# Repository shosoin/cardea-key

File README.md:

# Cardea Key

> *Cardea*, Roman goddess of hinges and thresholds: "her power is to open what is shut and to shut
> what is open" (Ovid, *Fasti* VI).

**Cardea Key** is an open-source security key firmware for the **Raspberry Pi Pico 2** (RP2350). It
combines in a single firmware what usually needs several keys:

- **FIDO2 / WebAuthn passkeys** and **U2F** — passwordless login, second factor, SSH `-sk` keys,
  `pam_u2f`, LUKS (`systemd-cryptenroll`).
- **OpenPGP card** — GnuPG signing, encryption and SSH authentication keys on the key.
- **PIV** — X.509 smart card (VPN client certificates, PKCS#11, Windows smart-card login).
- **OATH** (TOTP/HOTP) — authenticator codes, readable with `ykman oath` / Yubico Authenticator.
- **OTP slots** — static password, HOTP and HMAC-SHA1 challenge-response (e.g. KeePassXC), with
  touch support.
- **Vault** — encrypted, restorable backups of your passkeys, signed off by a CA you control.

Website: <https://cardeakey.org>

> **Status: experimental prototype, not audited.** Phase 0 (one unified firmware, tested on a bare
> Pico 2) and phase 1 (NXP SE051 secure element support) are released as **v0.3.0**. Phase 1 has
> been validated against a simulated SE05x only, **not yet on a real SE051C2** chip. Do not rely on
> it as your only key. Next: tests on the real chip, then a fingerprint sensor. See
> [Roadmap](#roadmap).

## How it is built

Cardea Key is built on the excellent work of **Pol Henarejos**:
[pico-fido](https://github.com/polhenarejos/pico-fido),
[pico-openpgp](https://github.com/polhenarejos/pico-openpgp) and
[pico-keys-sdk](https://github.com/polhenarejos/pico-keys-sdk). It is not affiliated with or
endorsed by the Pico Keys project.

This repository does not fork them. It pins each upstream repository to an exact commit
(`scripts/fetch-sources.sh`) and applies a reviewed set of patches (`patches/`, described in
[patches/README.md](patches/README.md)) to merge both applications into one firmware and to fix
the issues we found while testing, among them:

- **The firmware never writes the RP2350 OTP** unless you explicitly build with
  `HARDEN_HARDWARE=ON`. Upstream writes and locks OTP keys on first boot, which is irreversible.
  With the default build your Pico 2 stays a generic, reusable board.
- **OTP challenge-response with touch over the HID keyboard**, in asynchronous mode as YubiKeys
  do (used for example by KeePassXC). Upstream denies it.
- Bugs we reported were fixed upstream by Pol within a day (user presence really required for
  sign-in, FIDO reset, U2F and OATH "touch" accounts; master-key restore requires the PIN; the
  3-wrong-PINs-per-power-up lock; OTP over HID no longer corrupting the card thread). We follow his
  `main` and dropped our own versions of those fixes; see
  [patches/README.md](patches/README.md#fixes-now-in-upstream-dropped-on-2026-11-02).
- **Vault** with a replaceable root CA (see [docs/vault.md](docs/vault.md)).

## Hardware

- Raspberry Pi **Pico 2** (RP2350). The BOOTSEL button is the user-presence button and the
  on-board LED shows the state: short blinks when idle, **steady on when the key is waiting for a
  touch**.
- Optional: an **NXP SE051C2** secure element on I2C0 (SDA GP4, SCL GP5, address 0x48), e.g. on a
  MIKROE-5392 "SE051 Plug & Trust Click" board, for the `se05x` firmware below.

## Building

Tested on Debian 13 with `arm-none-eabi-gcc` 14.2, CMake 3.31 and Ninja.

```sh
sudo apt install git cmake ninja-build gcc-arm-none-eabi libnewlib-arm-none-eabi \
                 build-essential python3 python3-cryptography
scripts/fetch-sources.sh            # clones upstream at the pinned commits and applies patches/
cmake -G Ninja -S firmware -B build/cardea-key -DPICO_BOARD=pico2 \
      -DPICO_SDK_PATH=$PWD/third_party/pico-sdk
cmake --build build/cardea-key      # -> build/cardea-key/cardea_key.uf2
```

Main build options (`-D<option>=ON|OFF`):

| Option | Default | Meaning |
|---|---|---|
| `HARDEN_HARDWARE` | **OFF** | ON = upstream behaviour: writes and locks OTP keys on first boot. **Irreversible.** |
| `ENABLE_VAULT` | ON | Passkey backups (inactive until each key is enrolled). OFF removes the code. |
| `KEYV2_VAULT_CA_CERT` | Cardea Key Vault CA | Root certificate (PEM) of the vault CA. Point it at your own CA. |
| `FORCE_BUTTON_WAIT` | ON | Require a real button press for user presence. |
| `CARDEA_SE` | `soft` | Secure-element backend. `soft`: no chip, same security and data as v0.1.0. `se05x`: NXP SE051 on I2C (see [Two firmwares](#two-firmwares-soft-and-se05x)). |
| `CARDEA_SE_FALLBACK` | **OFF** | `se05x` only. OFF: without the chip the key does not run (SE FAULT). ON (bench only): it runs on the flash keys instead. |
| `ENABLE_OATH_APP`, `ENABLE_OTP_APP` | ON | OATH and OTP-slot applications. |
| `USB_VID`, `USB_PID` | `0x1209`, `0x0001` | USB IDs (see below). |

## Two firmwares: `soft` and `se05x`

Each release has two builds. **Both are experimental.**

| | `cardea_key-vX.Y.Z-soft.uf2` | `cardea_key-vX.Y.Z-se05x.uf2` |
|---|---|---|
| Hardware | a bare Pico 2 | Pico 2 **plus an SE051C2** wired to GP4/GP5 |
| Root key | master key in the Pico's flash | inside the SE051 (key derivation runs in the chip) |
| PINs and retry counters | in the Pico's flash | inside the SE051 (authentication objects with their own counter; the PIN never crosses the bus) |
| Link to the chip | — | encrypted and authenticated (Platform SCP03) |
| Without the chip | n/a | **SE FAULT**: the key refuses to work (see below) |
| Tested | on the board, all applications | against a simulated SE05x only, not yet on a real chip |

**What the `se05x` build does not do yet.** It runs in *test mode*: the SCP03 channel uses the
SE051C2 factory keys (public), and the master key is also kept in the flash, so that losing the
chip during development does not lose the data. **Today it protects no more than `soft`.** Leaving
test mode (per-device channel keys, root key generated in the chip and removed from the flash)
comes after the real-chip tests.

**SE FAULT.** If the `se05x` build finds no SE051 at power-up (or the root key is not in it), no
application answers, the USB product name ends in "SE FAULT" (it shows up as such in the
smart-card reader name), and the LED flashes three times quickly, then pauses. Nothing is erased:
plug the chip back in and power-cycle. A key in SE FAULT can still be rebooted into BOOTSEL with
`scripts/cardea-bootsel.sh`.

Switching between the two builds on the same Pico keeps the data, but once a PIN has moved into
the chip, the `soft` build can no longer check it.

## Flashing

Download the build you want from the [latest release](https://github.com/shosoin/cardea-key/releases/latest)
(check its SHA-256 in `SHA256SUMS`) or build it yourself. Hold BOOTSEL while plugging the Pico 2
in, then copy the `.uf2` file to the `RP2350` drive. Data
on the key (PIN, credentials) survives firmware updates. A key already running Cardea Key can be
rebooted into BOOTSEL with `scripts/cardea-bootsel.sh` (needs a button press).

## USB IDs and host software

The prototype uses the **pid.codes test ID `1209:0001`**. FIDO2 works out of the box (browsers,
`libfido2`, `python-fido2`). The smart-card applications (OpenPGP, PIV, OATH) go through CCID:
`pcscd`'s CCID driver only loads for known IDs, so add the test ID to its list
(`scripts/libccid-reader.py`, needs root) or use GnuPG's internal CCID driver.

This project **never ships with Yubico's vendor ID**. Some Yubico tools (`ykman otp`) only talk to
keys with that ID; changing the ID in your own build is your choice and your responsibility.

## Vault (passkey backups)

Passkeys normally die with the key. The vault lets you export them, encrypted with a vault key you
keep, and import them into another key enrolled in the same vault. Enrolling a key requires its
PIN, a 10-second button press right after plugging it in, and a certificate for that key's serial
number signed by the vault CA, which is compiled into the firmware. You can build with your own
CA. Details and the `scripts/cardea-vault.py` tool: [docs/vault.md](docs/vault.md).

## Documentation

- [docs/applications.md](docs/applications.md) — what each application is for and how to use it.
- [docs/vault.md](docs/vault.md) — vault design, own CA, enrollment, export and import.
- [patches/README.md](patches/README.md) — every change made to upstream, and why.
- [SECURITY.md](SECURITY.md) — threat model of the prototype and how to report a vulnerability.

## Roadmap

| Phase | What | Status |
|---|---|---|
| 0 | Unify pico-fido and pico-openpgp in one firmware; test on a bare Pico 2 without touching OTP | **done** |
| 1 | NXP SE051C2 secure element: PIN and retry counter in the SE, root key out of the flash | **done** on a simulated chip (v0.2.0; v0.3.0 follows upstream `main`); real-chip tests pending |
| 2 | Fingerprint sensor as user presence, time-limited biometric unlock | planned |
| 3 | Full prototype: Pico 2 + real SE051C2 + fingerprint sensor, tested together as one key | parts on the way |
| 4 | Own PCB (RP2354A + SE051C2 + sensor connector) | **design in progress**: [rev A draft](hardware/README.md), schematic done, placement draft, not routed; manufactured only after phase 3 |

## License

[AGPL-3.0](LICENSE), the license of the upstream projects. Patches and tools in this repository
are released under the same license. The hardware design files in [hardware/](hardware/README.md)
are licensed under [CERN-OHL-S-2.0](hardware/LICENSE). "Pico Keys" is a trademark of its owner; this project does
not use that name.

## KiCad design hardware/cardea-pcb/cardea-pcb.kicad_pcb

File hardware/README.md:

# Cardea Key — hardware (rev A, draft)

> **Work in progress. Not manufactured, not validated.** This is the first draft of Cardea Key's
> own board: the schematic passes KiCad's ERC, and the parts are placed but **not routed yet**.
> It will not be manufactured until the full prototype (Pico 2 + real SE051C2 + fingerprint
> sensor) has been validated. Do not order it.

| | |
|---|---|
| MCU | Raspberry Pi **RP2354A** (RP2350 with 2 MB flash inside) |
| Secure element | NXP **SE051C2** on I2C0 (GP4 SDA, GP5 SCL), with enable (GP6) and reset (GP7) from the MCU |
| Fingerprint sensor | off-board **R502-F Pro**, wires soldered into six 2.54 mm through holes (optional SH1.0 connector in parallel) |
| USB | USB-C receptacle (16 pins) on the board edge, VBUS TVS |
| Power | Diodes AP2112K-3.3 LDO |
| Board | 4 layers, 1.6 mm, about 45 × 20 mm, no screw holes (held by a 3D-printed case) |
| User interface | one push button (C&K KMR2) and an RGB LED; BOOTSEL; SWD on three 2.54 mm holes |

The RP2354A core (core regulator, crystal, decoupling, USB and BOOTSEL) follows Raspberry Pi's
**"RP2350A Minimal"** reference design (© Raspberry Pi Ltd, MIT licence) and the "Hardware design
with RP2350" guide.

## Files

- [`cardea-pcb-schematic-revA.pdf`](cardea-pcb-schematic-revA.pdf): the schematic.
- `cardea-pcb/`: the KiCad 10 project. `cardea-pcb.kicad_sch` is **generated** by
  `tools/gen_schematic.py` from a parts-and-nets table, so the netlist is exactly that table.
  `cardea-pcb.kicad_pcb` is the placement draft from `tools/gen_board.py`. `lib/cardea.kicad_sym`
  holds the SE051C2 symbol, drawn from its datasheet pin table.
- `tools/kicad_lib.py`: reads KiCad library symbols and their pins without KiCad's Python API.
- `images/`: renders of the current draft ([top](images/cardea-pcb-top.png),
  [bottom](images/cardea-pcb-bottom.png)).

```sh
python3 hardware/tools/gen_schematic.py
kicad-cli sch erc --severity-all hardware/cardea-pcb/cardea-pcb.kicad_sch      # must report 0
```

## Licence

The hardware design files in this directory are licensed under the
**CERN Open Hardware Licence Version 2 – Strongly Reciprocal** ([CERN-OHL-S-2.0](LICENSE)).
The firmware and the tools elsewhere in this repository stay under AGPL-3.0.

Symbols and footprints come from the official KiCad libraries (CC-BY-SA 4.0 with their exception
for designs), except the SE051C2 symbol, which is our own.

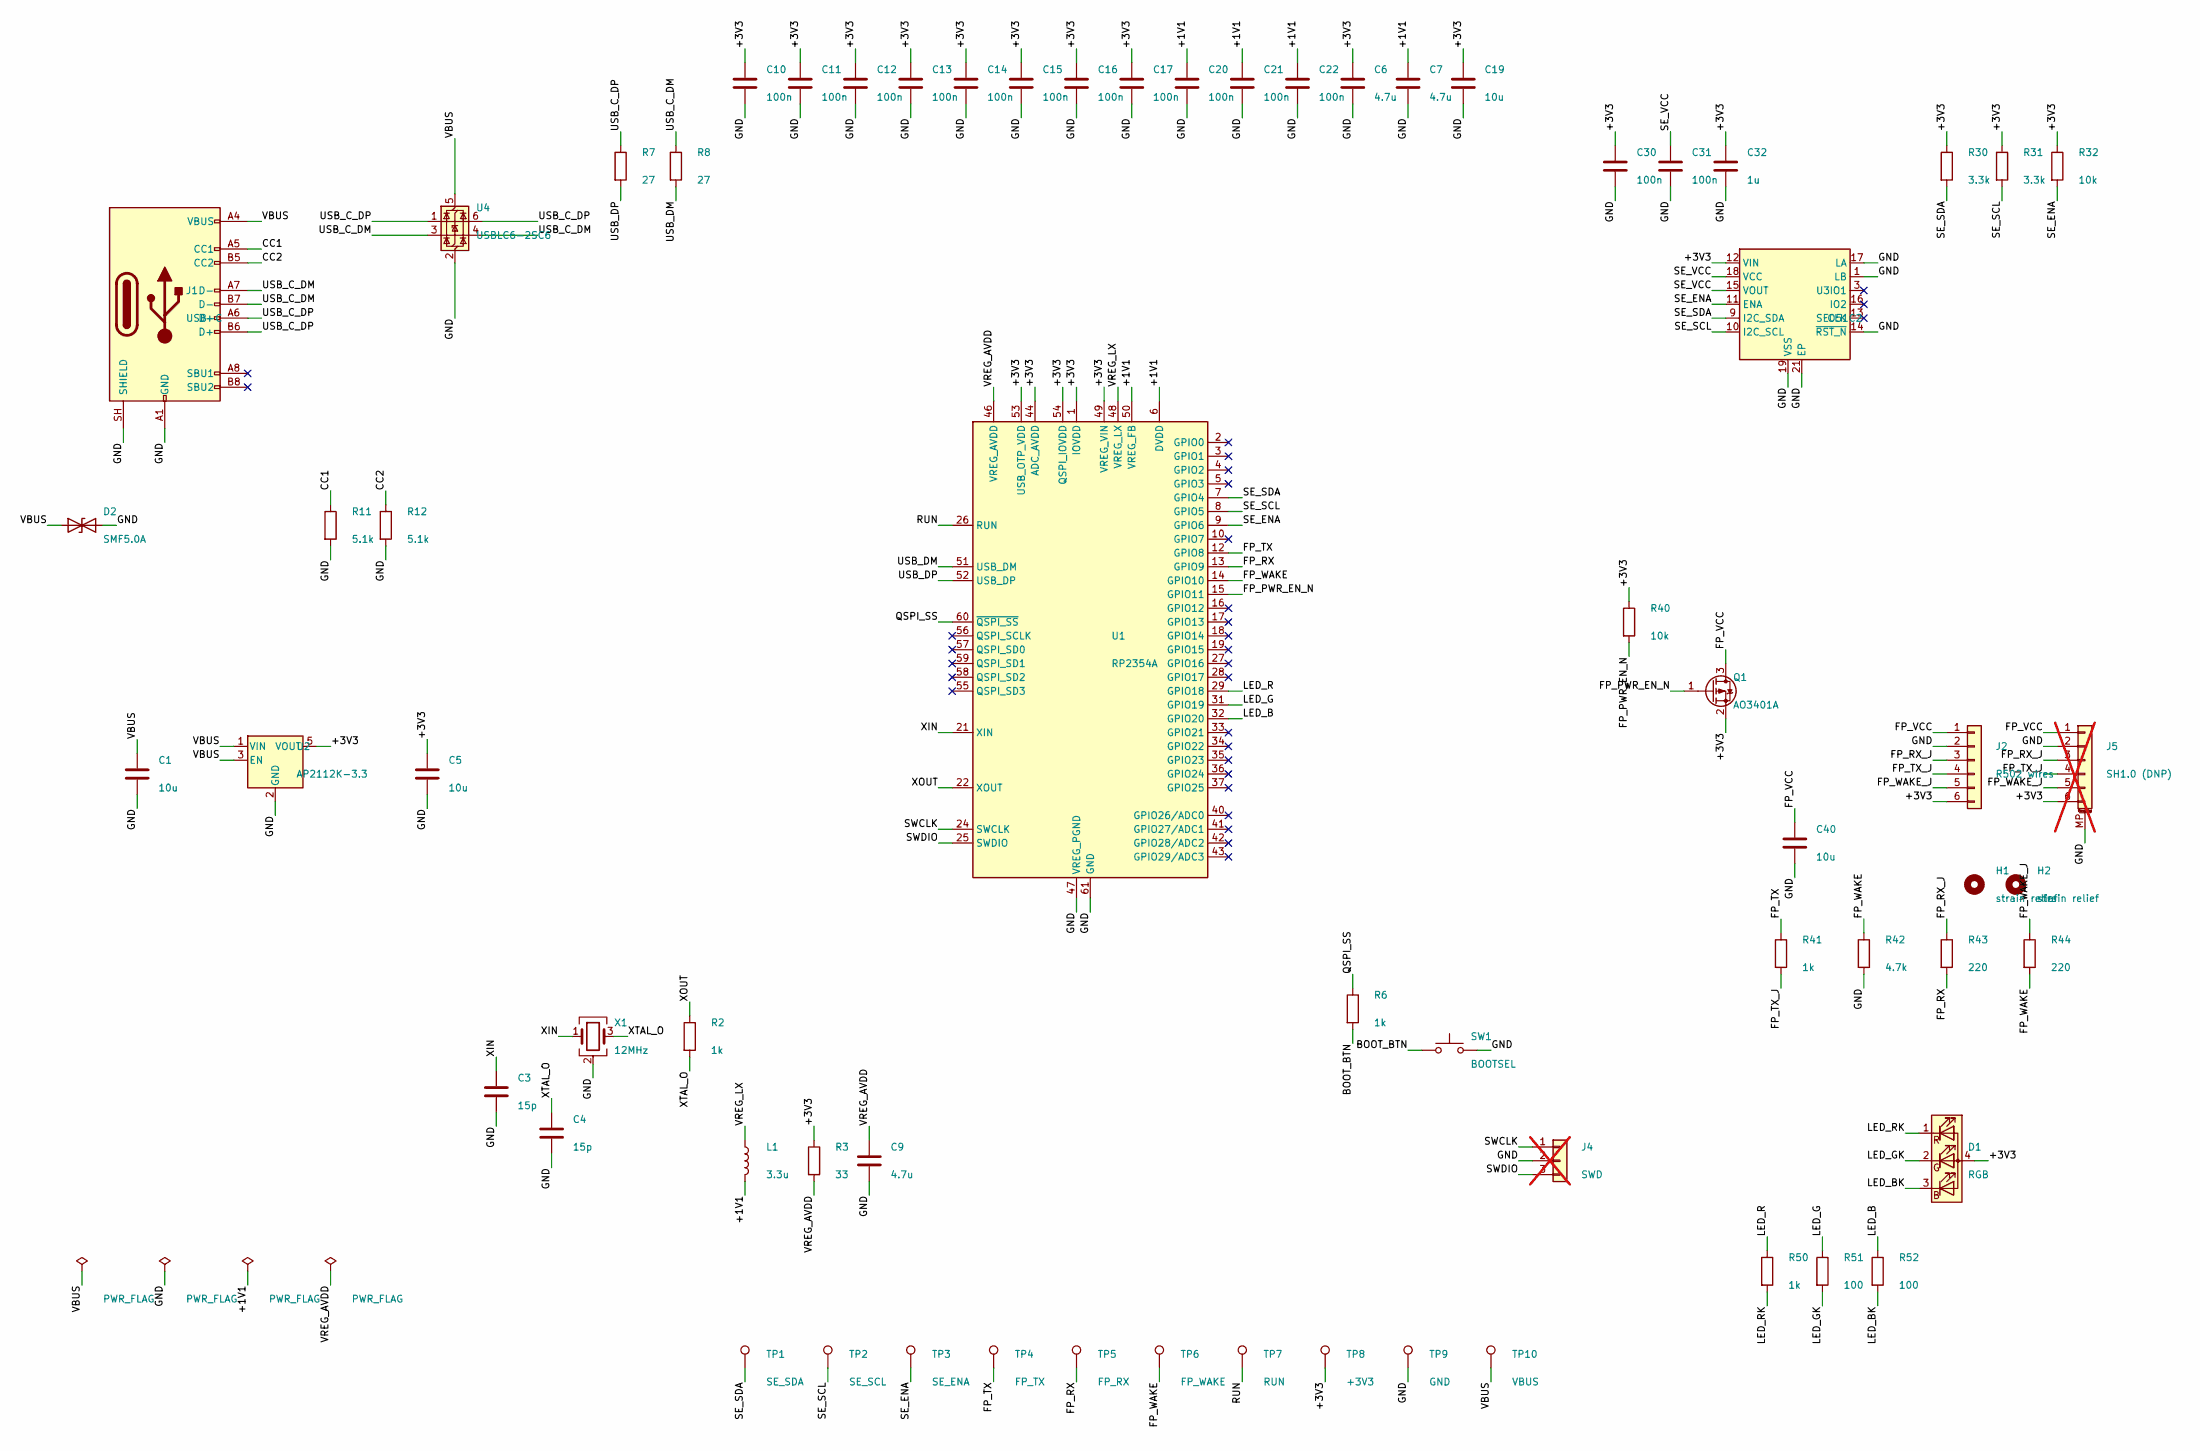
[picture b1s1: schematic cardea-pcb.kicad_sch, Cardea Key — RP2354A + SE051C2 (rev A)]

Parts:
C1, C5, C19, C40: 10u; C_0805_2012Metric; MPN CL21A106KAYNNNE; LCSC C15850
C3, C4: 15p; C_0402_1005Metric; LCSC C1548
C6, C7, C9: 4.7u; C_0402_1005Metric; LCSC C23733
C10, C11, C12, C13, C14, C15, C16, C17, C20, C21, C22, C30, C31: 100n; C_0402_1005Metric; LCSC C1525
C32: 1u; C_0402_1005Metric; MPN CL05A105KA5NQNC; LCSC C52923
D1: RGB; LED_RGB_1210
D2: SMF5.0A; D_SOD-123F; MPN SMF5.0A; LCSC C151296
H1, H2: strain relief; MountingHole_2.1mm
J1: USB-C; USB_C_Receptacle_HRO_TYPE-C-31-M-12; MPN TYPE-C-31-M-12; LCSC C165948
J2: R502 wires; PinHeader_1x06_P2.54mm_Vertical
J4: SWD; PinHeader_1x03_P2.54mm_Vertical; not fitted
J5: SH1.0 (DNP); JST_SH_SM06B-SRSS-TB_1x06-1MP_P1.00mm_Horizontal; MPN SM06B-SRSS-TB(LF)(SN); LCSC C160405; not fitted
L1: 3.3u; L_Abracon_AOTA-B201610S; MPN AOTA-B201610S3R3-101-T; LCSC C42411119
Q1: AO3401A; SOT-23; LCSC C15127
R2, R6, R41, R50: 1k; R_0402_1005Metric; LCSC C11702
R3: 33; R_0402_1005Metric; LCSC C25105
R7, R8: 27; R_0402_1005Metric; LCSC C25100
R11, R12: 5.1k; R_0402_1005Metric; LCSC C25905
R30, R31: 3.3k; R_0402_1005Metric; LCSC C25890
R32, R40: 10k; R_0402_1005Metric; LCSC C25744
R42: 4.7k; R_0402_1005Metric; LCSC C25900
R43, R44: 220; R_0402_1005Metric; LCSC C25091
R51, R52: 100; R_0402_1005Metric; LCSC C25076
SW1: BOOTSEL; SW_Push_1P1T_NO_CK_KMR2; MPN KMR221GLFS; LCSC C72443
TP1: SE_SDA; TestPoint_Pad_D1.0mm
TP2: SE_SCL; TestPoint_Pad_D1.0mm
TP3: SE_ENA; TestPoint_Pad_D1.0mm
TP4: FP_TX; TestPoint_Pad_D1.0mm
TP5: FP_RX; TestPoint_Pad_D1.0mm
TP6: FP_WAKE; TestPoint_Pad_D1.0mm
TP7: RUN; TestPoint_Pad_D1.0mm
TP8: +3V3; TestPoint_Pad_D1.0mm
TP9: GND; TestPoint_Pad_D1.0mm
TP10: VBUS; TestPoint_Pad_D1.0mm
U1: RP2354A; QFN-60-1EP_7x7mm_P0.4mm_EP3.4x3.4mm; MPN SC1511-A4; LCSC C41378174
U2: AP2112K-3.3; SOT-23-5; MPN AP2112K-3.3TRG1; LCSC C51118
U3: SE051C2; QFN-20-1EP_3x3mm_P0.4mm_EP1.65x1.65mm; MPN SE051C2HQ1/Z01XDZ; LCSC C5202100
U4: USBLC6-2SC6; SOT-23-6; MPN USBLC6-2SC6; LCSC C7519
X1: 12MHz; Crystal_SMD_3225-4Pin_3.2x2.5mm; MPN ABM8-272-T3; LCSC C20625731

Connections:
+1V1: C7.1, C20.1, C21.1, C22.1, L1.2, U1.6 (DVDD), U1.23 (DVDD), U1.39 (DVDD), U1.50 (VREG_FB)
+3V3: C5.1, C6.1, C10.1, C11.1, C12.1, C13.1, C14.1, C15.1, C16.1, C17.1, C19.1, C30.1, C32.1, D1.4 (A), J2.6, J5.6, Q1.2 (S), R3.1, R30.1, R31.1, R32.1, R40.1, TP8.1, U1.1 (IOVDD), U1.11 (IOVDD), U1.20 (IOVDD), U1.30 (IOVDD), U1.38 (IOVDD), U1.44 (ADC_AVDD), U1.45 (IOVDD), U1.49 (VREG_VIN), U1.53 (USB_OTP_VDD), U1.54 (QSPI_IOVDD), U2.5 (VOUT), U3.12 (VIN)
BOOT_BTN: R6.2, SW1.1
CC1: J1.A5 (CC1), R11.1
CC2: J1.B5 (CC2), R12.1
FP_PWR_EN_N: Q1.1 (G), R40.2, U1.15 (GPIO11)
FP_RX: R43.2, TP5.1, U1.13 (GPIO9)
FP_RX_J: J2.3, J5.3, R43.1
FP_TX: R41.1, TP4.1, U1.12 (GPIO8)
FP_TX_J: J2.4, J5.4, R41.2
FP_VCC: C40.1, J2.1, J5.1, Q1.3 (D)
FP_WAKE: R42.1, R44.2, TP6.1, U1.14 (GPIO10)
FP_WAKE_J: J2.5, J5.5, R44.1
GND: C1.2, C3.2, C4.2, C5.2, C6.2, C7.2, C9.2, C10.2, C11.2, C12.2, C13.2, C14.2, C15.2, C16.2, C17.2, C19.2, C20.2, C21.2, C22.2, C30.2, C31.2, C32.2, C40.2, D2.2 (A2), J1.A1 (GND), J1.A12 (GND), J1.B1 (GND), J1.B12 (GND), J1.SH (SHIELD), J2.2, J4.2, J5.2, J5.MP (MountPin), R11.2, R12.2, R42.2, SW1.2, TP9.1, U1.47 (VREG_PGND), U1.61 (GND), U2.2 (GND), U3.1 (LB), U3.14 (~RST_N), U3.17 (LA), U3.19 (VSS), U3.21 (EP), U4.2 (GND), X1.2 (G), X1.4 (G)
LED_B: R52.1, U1.32 (GPIO20)
LED_BK: D1.3 (BK), R52.2
LED_G: R51.1, U1.31 (GPIO19)
LED_GK: D1.2 (GK), R51.2
LED_R: R50.1, U1.29 (GPIO18)
LED_RK: D1.1 (RK), R50.2
QSPI_SS: R6.1, U1.60 (~QSPI_SS)
RUN: TP7.1, U1.26 (RUN)
SE_ENA: R32.2, TP3.1, U1.9 (GPIO6), U3.11 (ENA)
SE_SCL: R31.2, TP2.1, U1.8 (GPIO5), U3.10 (I2C_SCL)
SE_SDA: R30.2, TP1.1, U1.7 (GPIO4), U3.9 (I2C_SDA)
SE_VCC: C31.1, U3.15 (VOUT), U3.18 (VCC)
SWCLK: J4.1, U1.24 (SWCLK)
SWDIO: J4.3, U1.25 (SWDIO)
USB_C_DM: J1.A7 (D-), J1.B7 (D-), R8.1, U4.3 (I/O2), U4.4 (I/O2)
USB_C_DP: J1.A6 (D+), J1.B6 (D+), R7.1, U4.1 (I/O1), U4.6 (I/O1)
USB_DM: R8.2, U1.51 (USB_DM)
USB_DP: R7.2, U1.52 (USB_DP)
VBUS: C1.1, D2.1 (A1), J1.A4 (VBUS), J1.A9 (VBUS), J1.B4 (VBUS), J1.B9 (VBUS), TP10.1, U2.1 (VIN), U2.3 (EN), U4.5 (VBUS)
VREG_AVDD: C9.1, R3.2, U1.46 (VREG_AVDD)
VREG_LX: L1.1, U1.48 (VREG_LX)
XIN: C3.1, U1.21 (XIN), X1.1
XOUT: R2.1, U1.22 (XOUT)
XTAL_O: C4.1, R2.2, X1.3

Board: 4 copper layers, 67 parts (18 on the bottom side), 38 nets, no tracks yet.

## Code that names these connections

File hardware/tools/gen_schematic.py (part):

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two("C5", "C", "10u", (93.98, 162.56), "+3V3", "GND", fp=FP_C0805, LCSC="C15850", MPN="CL21A106KAYNNNE")

# ---- RP2354A (2 MB flash in package) ----------------------------------------------------------
GPIO_NETS = {4: "SE_SDA", 5: "SE_SCL", 6: "SE_ENA", 8: "FP_TX", 9: "FP_RX", 10: "FP_WAKE", 11: "FP_PWR_EN_N",
             18: "LED_R", 19: "LED_G", 20: "LED_B"}
u1 = {"1": "+3V3", "11": "+3V3", "20": "+3V3", "30": "+3V3", "38": "+3V3", "45": "+3V3",
      "6": "+1V1", "23": "+1V1", "39": "+1V1",
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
